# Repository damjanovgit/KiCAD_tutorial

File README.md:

# KiCAD_tuturiual
KiCAD project made for educational purpuses.

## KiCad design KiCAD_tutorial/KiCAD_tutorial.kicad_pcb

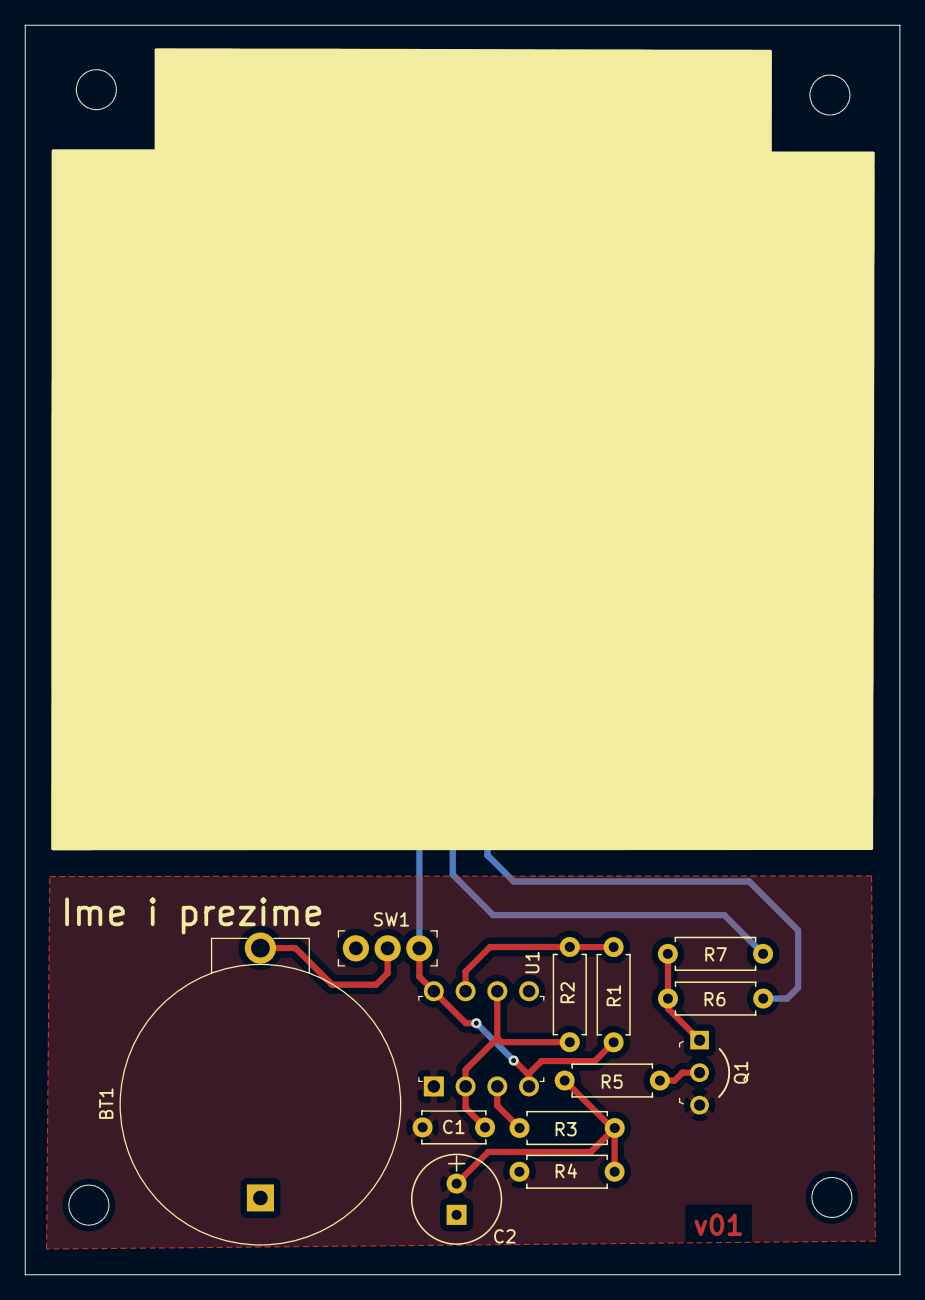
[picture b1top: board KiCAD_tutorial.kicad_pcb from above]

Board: 2 copper layers, 70.0 x 100.0 mm, 19 parts (0 on the bottom side), 10 nets.

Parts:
 : MountingHole_3.2mm_M3
 #2,  #3,  #4: MountingHole_3.2mm_M3
BT1: Battery_Cell; Battery_Holder_Coin_2032_BS-7
C1: 1uF; C_Disc_D5.0mm_W2.5mm_P5.00mm
C2: 100uF; CP_Radial_Tantal_D7.0mm_P2.50mm
D1, D2: LED; LED_D5.0mm
Q1: BC547; TO-92-3_Formed_Leads
R1, R3: 22k; R_Axial_DIN0207_L6.3mm_D2.5mm_P7.62mm_Horizontal
R2: 330k; R_Axial_DIN0207_L6.3mm_D2.5mm_P7.62mm_Horizontal
R4: 100k; R_Axial_DIN0207_L6.3mm_D2.5mm_P7.62mm_Horizontal
R5: 10k; R_Axial_DIN0207_L6.3mm_D2.5mm_P7.62mm_Horizontal
R6, R7: 100; R_Axial_DIN0207_L6.3mm_D2.5mm_P7.62mm_Horizontal
SW1: SW_DPDT_x2; PinHeader_1x3_P2.54_Drill1.1mm
U1: 555_Timer; DIP-8_W7.62mm

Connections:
GND: C1.2, C2.1, Q1.3, R4.1, U1.1
unnamed: C1.1, R2.2, U1.2, U1.6
unnamed: C2.2, R3.1, R4.2, R5.2
unnamed: D1.1, R6.1
unnamed: D2.1, R7.1
unnamed: Q1.1, R6.2, R7.2
unnamed: Q1.2, R5.1
unnamed: R1.2, R2.1, U1.7
unnamed: R3.2, U1.3
VDD: D1.2, D2.2, R1.1, SW1.3, U1.4, U1.8

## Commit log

2021-10-24 KiCAD tutorijal
